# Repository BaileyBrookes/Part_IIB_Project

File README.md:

# Part IIB Project: Aircraft Performance Logger:
### Developing a cheap module using GPS and pressure sensor to measure accurately take-off distance required (TODR)
This is the enire project directory, files/folders of note are:

1. AircraftDataLogger - KiCad design files for PCB design

2. \Code\Arduino Sketches\Firmware - Firmware for the PCB

3. Code\TODR.py - Python script that calculates TODR and ground roll

4. Code\CheapDGPS2.py - Script investigating the DGPS idea, with data collected in preliminary testing

Other python scripts have been used in investigation and making plots.

For any clarification or help please email me at bailey.brookes@hotmail.co.uk

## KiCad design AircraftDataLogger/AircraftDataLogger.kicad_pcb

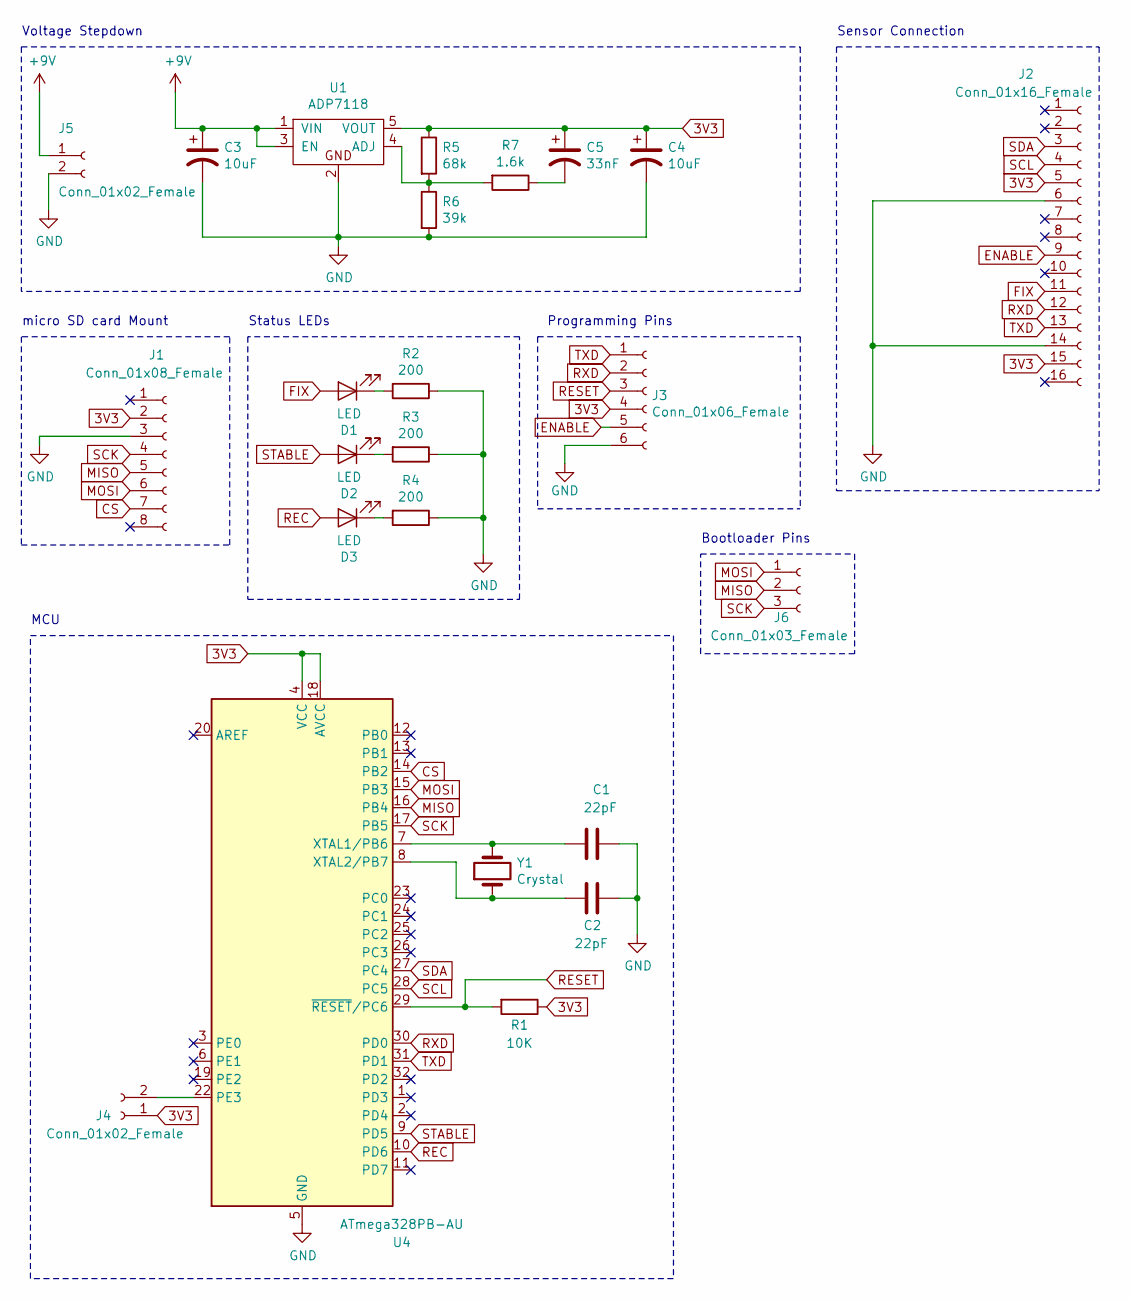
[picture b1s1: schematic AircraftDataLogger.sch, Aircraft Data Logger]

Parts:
C1, C2: 22pF; C_0805_2012Metric
C3, C4: 10uF; C_1210_3225Metric
C5: 33nF; C_0805_2012Metric
D1, D2, D3: LED; LED_D3.0mm_Clear
J1: Conn_01x08_Female; PinSocket_1x08_P2.54mm_Vertical
J2: Conn_01x16_Female; PinSocket_1x16_P2.54mm_Vertical
J3: Conn_01x06_Female; PinSocket_1x06_P2.54mm_Vertical
J4, J5: Conn_01x02_Female; PinSocket_1x02_P2.54mm_Vertical
J6: Conn_01x03_Female; PinSocket_1x03_P2.54mm_Vertical
R1: 10K; R_0805_2012Metric
R2, R3, R4: 200; R_0805_2012Metric
R5: 68k; R_0805_2012Metric
R6: 39k; R_0805_2012Metric
R7: 1.6k; R_0805_2012Metric
U1: ADP7118; TSOT-23-5
U4: ATmega328PB-AU; TQFP-32_7x7mm_P0.8mm
Y1: Crystal; Crystal_HC49-4H_Vertical

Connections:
3V3: C4.1, C5.1, J1.2, J2.5, J2.15, J3.4, J4.1, R1.1, R5.1, U1.5 (VOUT), U4.4 (VCC), U4.18 (AVCC)
+9V: C3.1, J5.1, U1.1 (VIN), U1.3 (EN)
CS: J1.7, U4.14 (PB2)
ENABLE: J2.9, J3.5
FIX: D1.2 (A), J2.11
GND: C1.1, C2.1, C3.2, C4.2, J1.3, J2.6, J2.14, J3.6, J5.2, R2.1, R3.1, R4.1, R6.2, U1.2, U4.5 (GND), U4.21 (GND)
MISO: J1.5, J6.2, U4.16 (PB4)
MOSI: J1.6, J6.1, U4.15 (PB3)
unnamed: C1.2, U4.7 (XTAL1/PB6), Y1.2
unnamed: C2.2, U4.8 (XTAL2/PB7), Y1.1
unnamed: C5.2, R7.1
unnamed: D1.1 (K), R2.2
unnamed: D2.1 (K), R3.2
unnamed: D3.1 (K), R4.2
unnamed: J4.2, U4.22 (PE3)
unnamed: R5.2, R6.1, R7.2, U1.4 (ADJ)
REC: D3.2 (A), U4.10 (PD6)
RESET: J3.3, R1.2, U4.29 (~RESET~/PC6)
RXD: J2.12, J3.2, U4.30 (PD0)
SCK: J1.4, J6.3, U4.17 (PB5)
SCL: J2.4, U4.28 (PC5)
SDA: J2.3, U4.27 (PC4)
STABLE: D2.2 (A), U4.9 (PD5)
TXD: J2.13, J3.1, U4.31 (PD1)

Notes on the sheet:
Voltage Stepdown
Sensor Connection
Status LEDs
Programming Pins
micro SD card Mount
MCU
Bootloader Pins

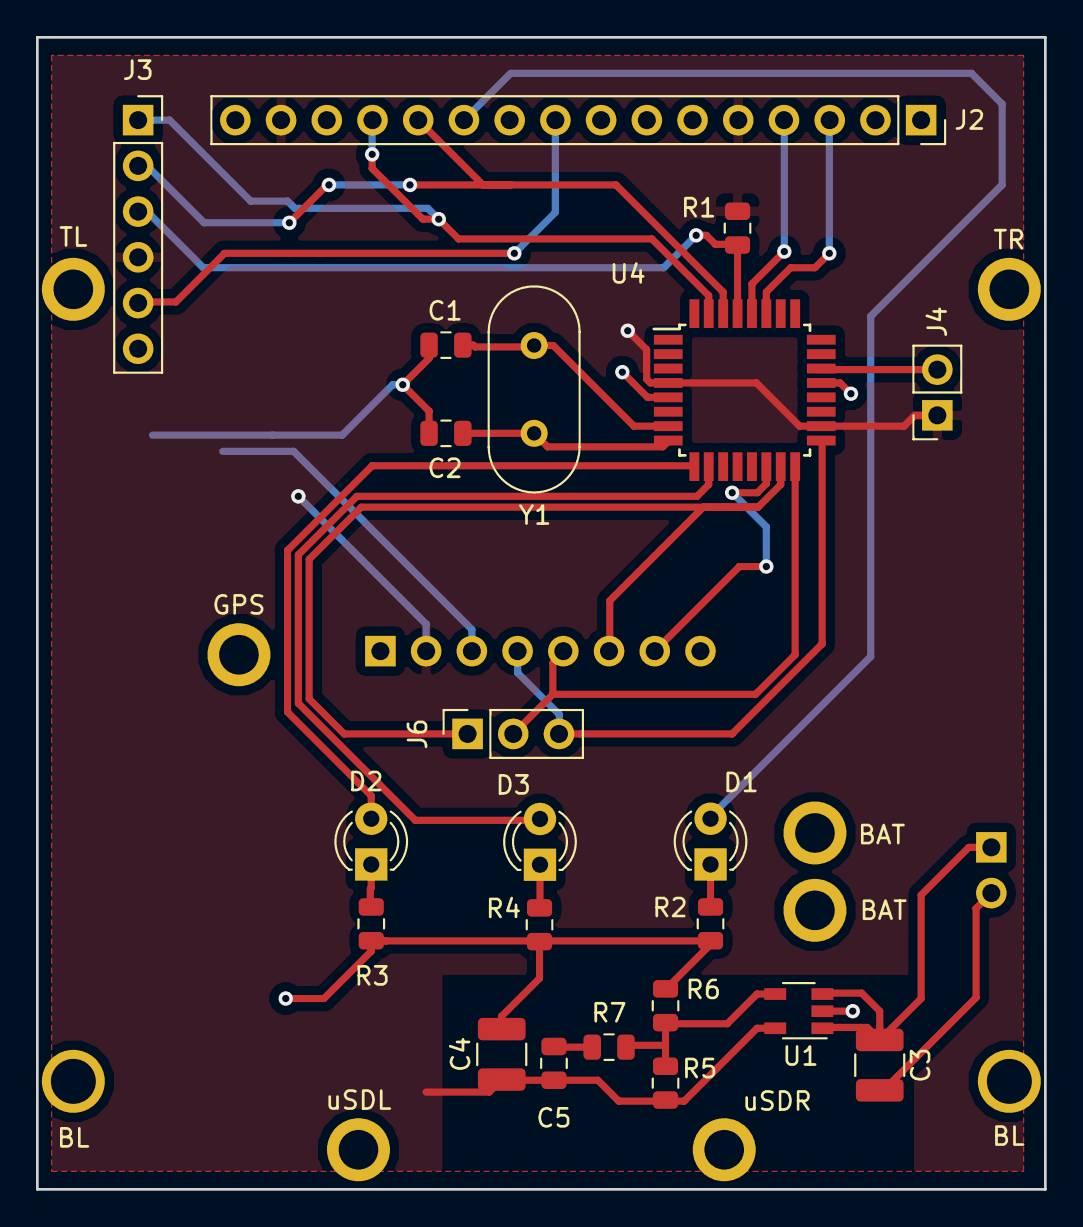
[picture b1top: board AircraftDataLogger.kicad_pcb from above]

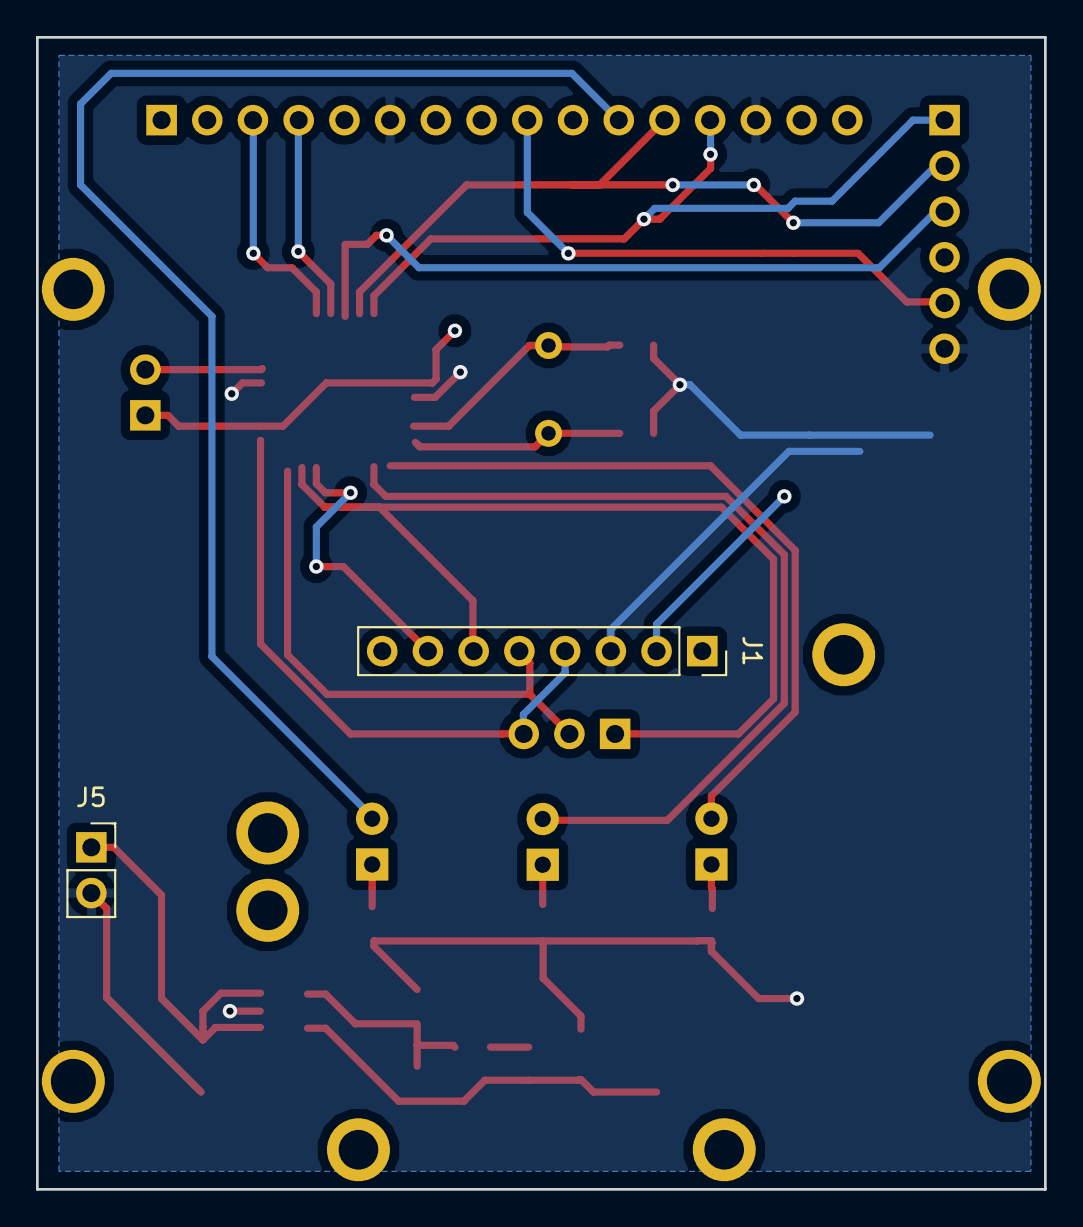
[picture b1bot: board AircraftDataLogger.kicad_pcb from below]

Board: 2 copper layers, 56.0 x 64.0 mm, 33 parts (2 on the bottom side), 24 nets.

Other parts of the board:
BAT: MountingHole_2.2mm_M2_ISO7380_Pad
BAT#2: MountingHole_2.2mm_M2_ISO7380_Pad
BL: MountingHole_2.2mm_M2_ISO7380_Pad
BL#2: MountingHole_2.2mm_M2_ISO7380_Pad
GPS: MountingHole_2.2mm_M2_ISO7380_Pad
TL: MountingHole_2.2mm_M2_ISO7380_Pad
TR: MountingHole_2.2mm_M2_ISO7380_Pad
uSDL: MountingHole_2.2mm_M2_ISO7380_Pad
uSDR: MountingHole_2.2mm_M2_ISO7380_Pad

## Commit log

2019-05-28 Submission commit
2019-06-10 Submi commit
2019-07-16 PDF of final report
2019-07-31 Rename README.txt to README_OLD.txt
